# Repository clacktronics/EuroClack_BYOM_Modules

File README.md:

# BYOM Modules

In this repository is all the modules in the book for **Build Your Own Modular** the Clacktronics ring binder product to build your own modular synthesizer from scratch. [clacktronics.co.uk/byom/](http://clacktronics.co.uk/byom/). These are the original project files PCB and panel With branding removed, they are not the pages which are panels I make up from these files. It does not include the text of the book either. I have provided these as a starting point for your own projects and ideas, I do not mind if they are used commercially, all I ask for is attribution to my original physical design and for them not to be sold under my brand name **Clacktronics**.

## PSU

A simple PSU that uses the 12V direct and creates a -12V using a cheap through hole MC34063

[PSU Schematic](pdf_schematics/BYOM_PSU_main.pdf)

## VCO

A paired down sawtooth VCO that can do a couple of octaves, uses only TL074

[VCO Schematic](pdf_schematics/BYOM_VCO_main.pdf)

## VCA

Simple dual VCA using the LM13700

[VCA Schematic](pdf_schematics/BYOM_VCA_main.pdf)

## VCF

A gritty sounding VCF using the LM13700

[VCF Schematic](pdf_schematics/BYOM_VCF_main.pdf)

## ATTENUVERTER

Performs basic attunuation and inversion of CV signals

[Attenuverter Schematic](pdf_schematics/BYOM_Attenuverter_main.pdf)

## MIXER

Mixes CV and Audio signals

[Mixer Schematic](pdf_schematics/BYOM_Mixer_main.pdf)

## LFO

Simple LFO that has shape and frequency controls

[LFO Schematic](pdf_schematics/BYOM_LFO_main.pdf)

## ENVELOPE

Simple AR generator

[Envelope Schematic](pdf_schematics/BYOM_Envelope_main.pdf)

## MICROCONTROLLER

Raspberry Pi Pico based experimental board

[Micro Schematic](pdf_schematics/BYOM_Micro_main.pdf)

## PASSIVE MULT

Helps connect CV outputs together

## POWER BUS

Simple passive power bus

## BLANK

Pretty blank plate

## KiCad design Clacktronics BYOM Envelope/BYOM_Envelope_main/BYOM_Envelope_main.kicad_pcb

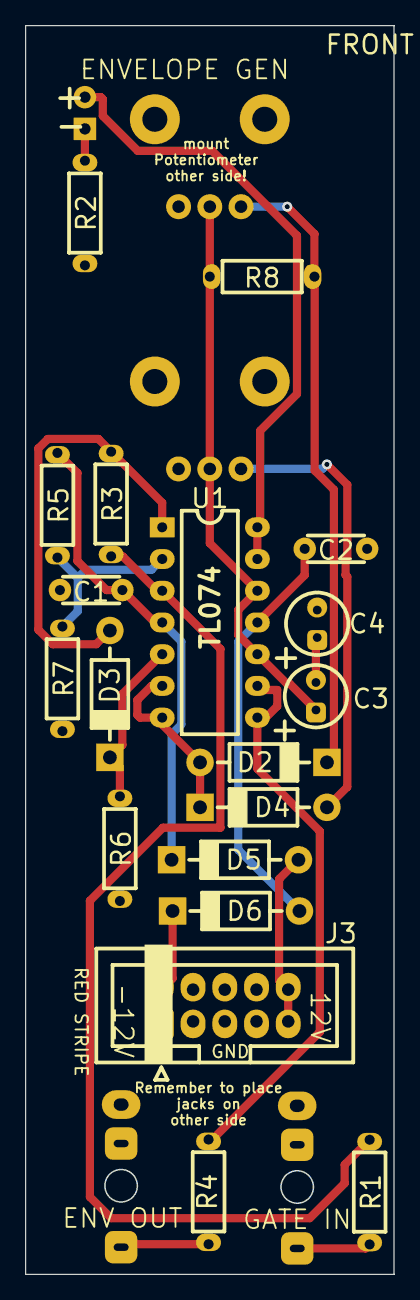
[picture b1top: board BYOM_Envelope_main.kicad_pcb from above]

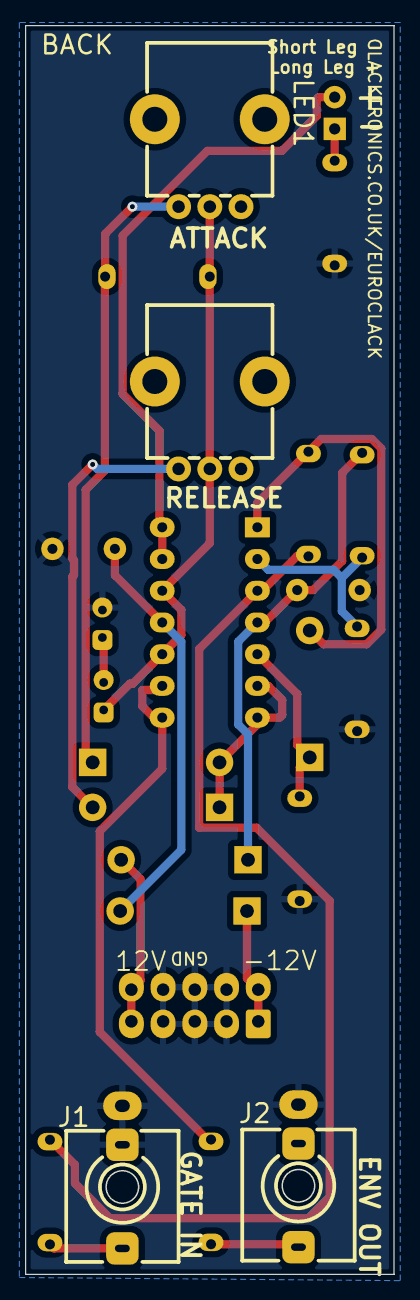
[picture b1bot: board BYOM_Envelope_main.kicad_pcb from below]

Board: 2 copper layers, 29.5 x 100.0 mm, 24 parts (5 on the bottom side), 19 nets.

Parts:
C1, C2: 100n; C_TH_Disc_P5.00mm
C3, C4: 100uF; C_TH_Elec_5mm_P2mm
D2, D3, D4, D5, D6: 1N5817; D_TH_DO-41_P10.16mm
J1: GATE_IN; Jack_3.5mm_QingPu_WQP-PJ398SM_Vertical
J2: AR_ENVELOPE_OUT; Jack_3.5mm_QingPu_WQP-PJ398SM_Vertical
J3: IDC 02x05 Header; IDC-Header_2x05_P2.54mm_Vertical
LED1: LED; LED_D3.0mm
R1, R5, R6: 100k; R_Axial_DIN0204_L3.6mm_D1.6mm_P7.62mm_Horizontal
R2, R4: 1k; R_Axial_DIN0204_L3.6mm_D1.6mm_P7.62mm_Horizontal
R3: 1M; R_Axial_DIN0204_L3.6mm_D1.6mm_P7.62mm_Horizontal
R7, R8: 10k; R_Axial_DIN0204_L3.6mm_D1.6mm_P7.62mm_Horizontal
RV1: Attack; POT_TH_Alps_RK09K_Single_Vertical
RV2: Release; POT_TH_Alps_RK09K_Single_Vertical
U1: TL074; DIP-14_W7.62mm_LongPads_copy

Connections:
+12V: C1.2, D5.1 (K), R5.2, U1.4 (V+)
-12V: C2.2, D6.2 (A), U1.11 (V-)
GND: C1.1, C2.1, C4.2, J1.S, J1.TN, J2.S, J3.3, J3.4, J3.5, J3.6, J3.7, J3.8, R2.1, R6.1, R7.1
unnamed: C3.2, C4.1
unnamed: D2.2 (A), D4.1 (K), U1.6 (-), U1.7
unnamed: D2.1 (K), R8.2, RV1.3
unnamed: D3.2 (A), R3.2, U1.1
unnamed: D3.1 (K), R6.2, U1.5 (+)
unnamed: D4.2 (A), RV2.3
unnamed: D5.2 (A), J3.9, J3.10
unnamed: D6.1 (K), J3.1, J3.2
unnamed: J1.T, R1.1
unnamed: J2.T, R4.2
unnamed: LED1.2 (A), U1.13 (-), U1.14
unnamed: LED1.1 (K), R2.2
unnamed: R1.2, R3.1, U1.3 (+)
unnamed: R5.1, R7.2, U1.2 (-)
unnamed: C3.1, R8.1, RV1.2, RV2.2, U1.10 (+), U1.12 (+)
unnamed: R4.1, U1.8, U1.9 (-)

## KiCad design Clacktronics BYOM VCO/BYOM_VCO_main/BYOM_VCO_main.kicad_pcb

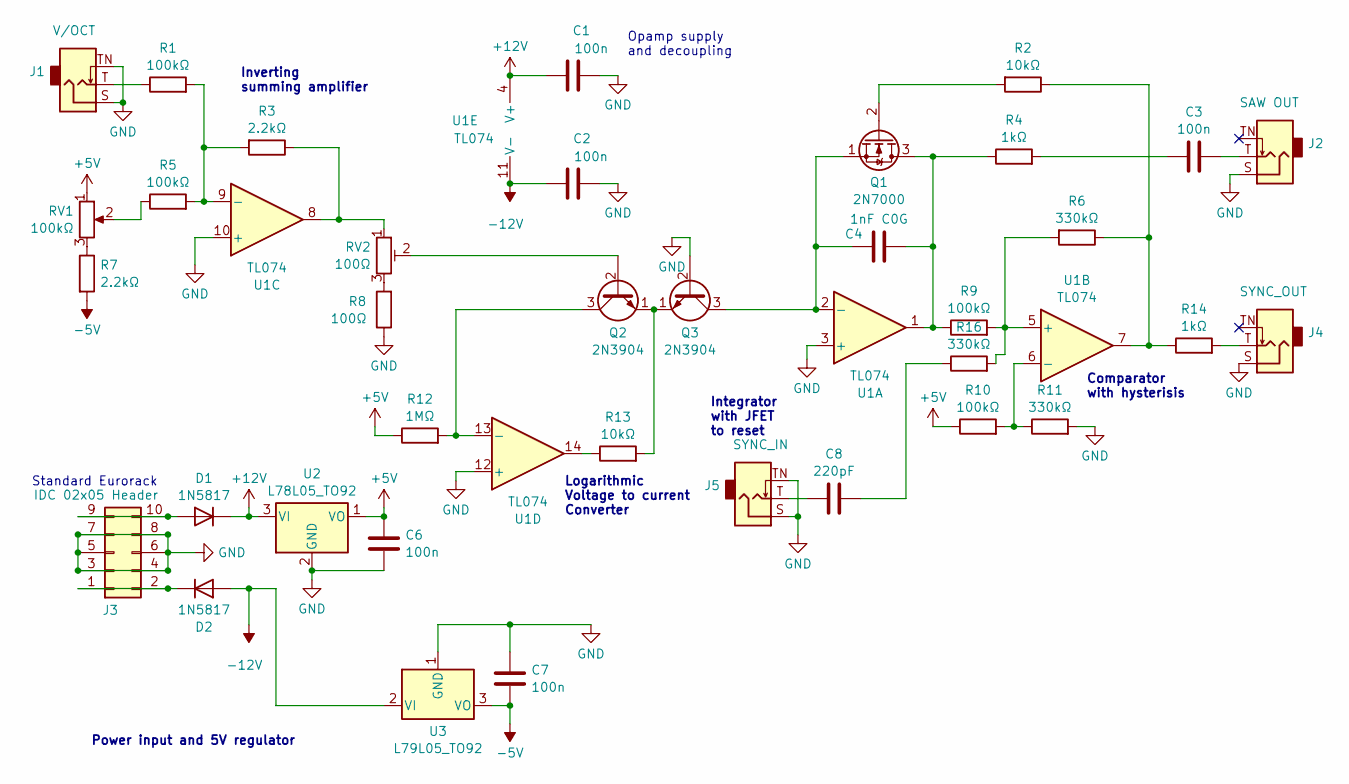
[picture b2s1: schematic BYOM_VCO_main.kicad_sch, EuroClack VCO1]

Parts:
C1, C2, C3, C6, C7: 100n; C_TH_Disc_P5.00mm
C4: 1nF C0G; C_TH_Disc_P5.00mm
C8: 220pF; C_TH_Disc_P5.00mm
D1, D2: 1N5817; D_TH_DO-41_P10.16mm
J1: V/OCT; Jack_3.5mm_QingPu_WQP-PJ398SM_Vertical
J2: SAW OUT; Jack_3.5mm_QingPu_WQP-PJ398SM_Vertical
J3: IDC 02x05 Header; IDC-Header_2x05_P2.54mm_Vertical
J4: SYNC_OUT; Jack_3.5mm_QingPu_WQP-PJ398SM_Vertical
J5: SYNC_IN; Jack_3.5mm_QingPu_WQP-PJ398SM_Vertical
Q1: 2N7000; TO-92_Inline_Wide
Q2, Q3: 2N3904; TO-92_Inline_Wide
R1, R5, R9, R10: 100kΩ; R_Axial_DIN0204_L3.6mm_D1.6mm_P7.62mm_Horizontal
R2, R13: 10kΩ; R_Axial_DIN0204_L3.6mm_D1.6mm_P7.62mm_Horizontal
R3, R7: 2.2kΩ; R_Axial_DIN0204_L3.6mm_D1.6mm_P7.62mm_Horizontal
R4, R14: 1kΩ; R_Axial_DIN0204_L3.6mm_D1.6mm_P7.62mm_Horizontal
R6, R11, R16: 330kΩ; R_Axial_DIN0204_L3.6mm_D1.6mm_P7.62mm_Horizontal
R8: 100Ω; R_Axial_DIN0204_L3.6mm_D1.6mm_P7.62mm_Horizontal
R12: 1MΩ; R_Axial_DIN0204_L3.6mm_D1.6mm_P7.62mm_Horizontal
RV1: 100kΩ; POT_TH_Alps_RK09K_Single_Vertical
RV2: 100Ω; Potentiometer_Bourns_3296W_Vertical
U1: TL074; DIP-14_W7.62mm_LongPads_copy
U2: L78L05_TO92; TO-92_Inline_Wide
U3: L79L05_TO92; TO-92_Inline_Wide

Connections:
+5V: C6.2, R10.1, R12.1, RV1.1, U2.1 (VO)
+12V: C1.2, D1.1 (K), U1.4 (V+), U2.3 (VI)
-5V: C7.1, R7.2, U3.3 (VO)
-12V: C2.2, D2.2 (A), U1.11 (V-), U3.2 (VI)
GND: C1.1, C2.1, C6.1, C7.2, J1.S, J1.TN, J2.S, J3.3, J3.4, J3.5, J3.6, J3.7, J3.8, J4.S, J5.S, J5.TN, Q3.2 (B), R8.1, R11.2, U1.3 (+), U1.10 (+), U1.12 (+), U2.2 (GND), U3.1 (GND)
unnamed: C3.1, R4.2
unnamed: C3.2, J2.T
unnamed: C8.1, J5.T
unnamed: C8.2, R16.1
unnamed: D1.2 (A), J3.9, J3.10
unnamed: D2.1 (K), J3.1, J3.2
unnamed: J1.T, R1.1
unnamed: J4.T, R14.2
unnamed: C4.2, Q1.3 (D), R4.1, R9.1, U1.1
unnamed: Q1.2 (G), R2.2
unnamed: C4.1, Q1.1 (S), Q3.3 (C), U1.2 (-)
unnamed: Q2.2 (B), RV2.2
unnamed: Q2.3 (C), R12.2, U1.13 (-)
unnamed: Q2.1 (E), Q3.1 (E), R13.2
unnamed: R3.1, RV2.1, U1.8
unnamed: R5.1, RV1.2
unnamed: R7.1, RV1.3
unnamed: R8.2, RV2.3
unnamed: R13.1, U1.14
unnamed: R2.1, R6.1, R14.1, U1.7
unnamed: R6.2, R9.2, R16.2, U1.5 (+)
unnamed: R10.2, R11.1, U1.6 (-)
unnamed: R1.2, R3.2, R5.2, U1.9 (-)

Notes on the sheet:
Standard Eurorack
Logarithmic Voltage to current Converter
Opamp supply and decoupling
Comparator with hysterisis
Power input and 5V regulator
Integrator with JFET to reset
Inverting summing amplifier

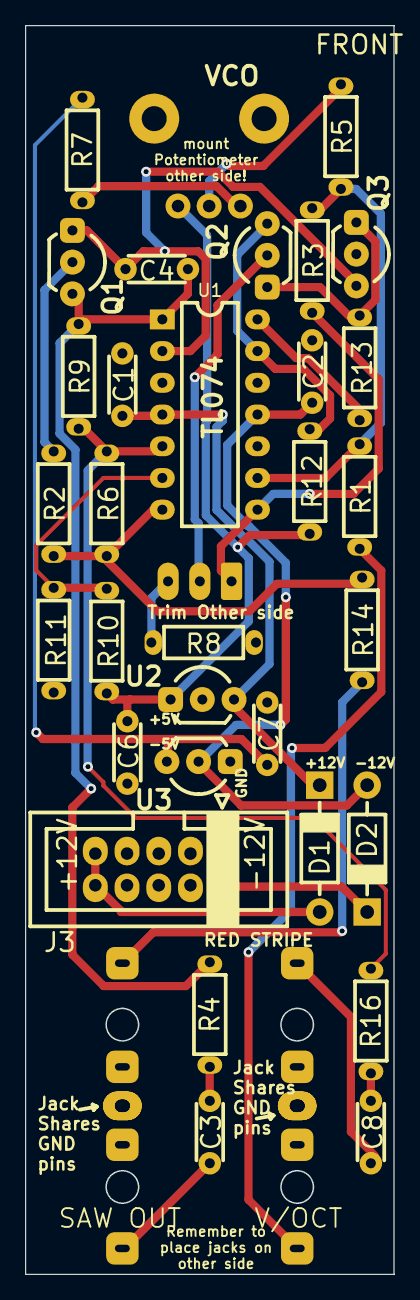
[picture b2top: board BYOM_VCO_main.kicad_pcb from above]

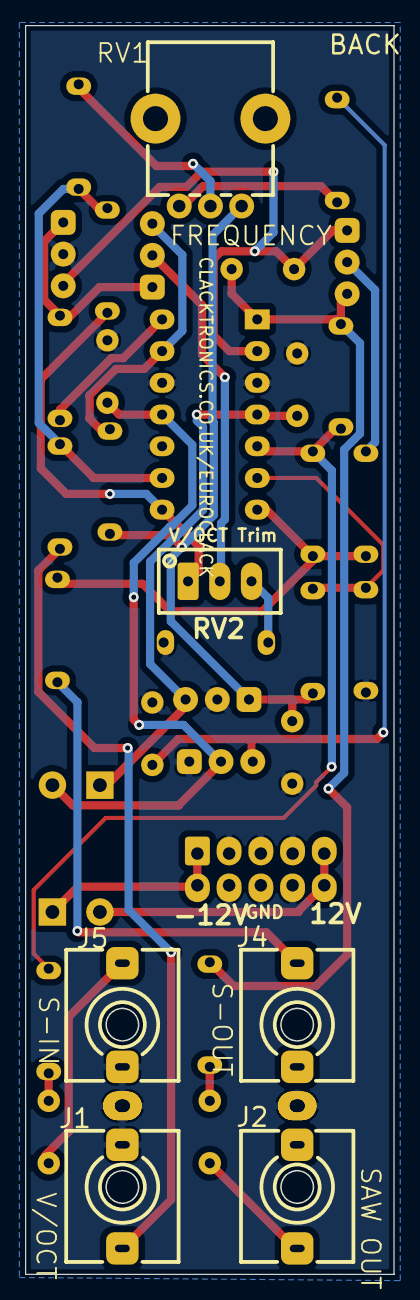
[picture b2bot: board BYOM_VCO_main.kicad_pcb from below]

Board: 2 copper layers, 29.5 x 100.0 mm, 37 parts (6 on the bottom side), 28 nets.

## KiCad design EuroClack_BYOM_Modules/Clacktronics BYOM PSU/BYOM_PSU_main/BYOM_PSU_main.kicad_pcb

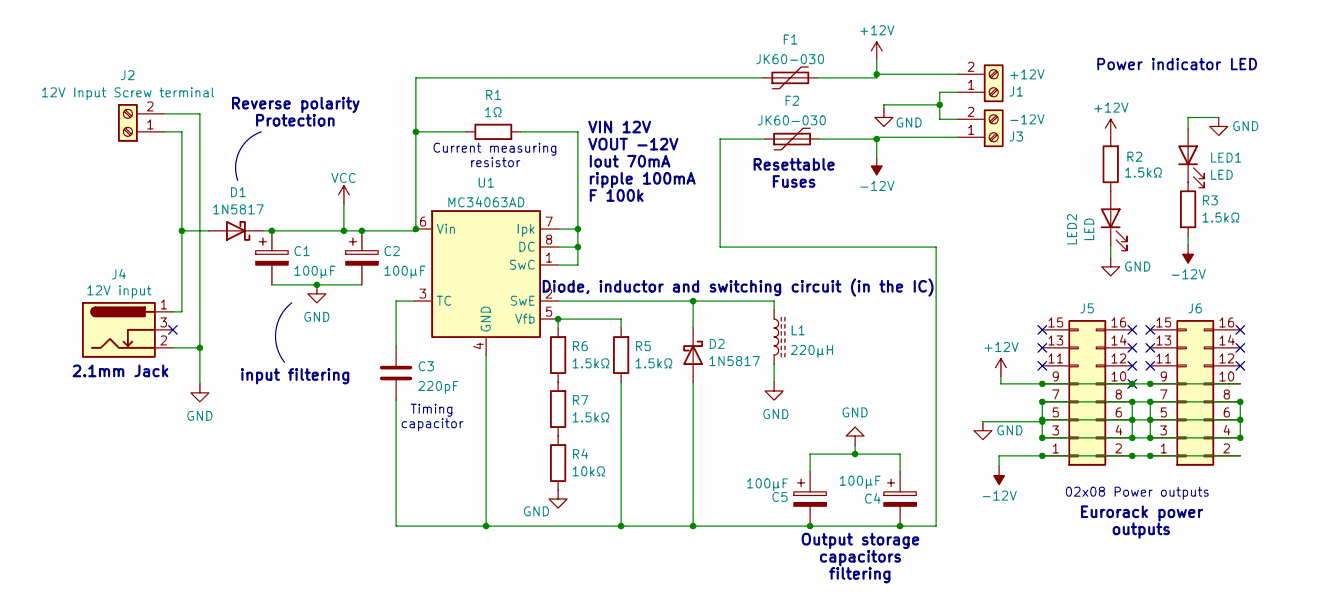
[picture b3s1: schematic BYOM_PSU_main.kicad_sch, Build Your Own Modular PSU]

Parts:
C1, C2, C4, C5: 100μF; C_TH_Elec_5mm_P2mm
C3: 220pF; C_TH_Disc_P5.00mm
D1, D2: 1N5817; D_TH_DO-41_P10.16mm
F1, F2: JK60-030; C_TH_Disc_P5.00mm
J1: +12V; 5.08 01X02
J2: 12V Input Screw terminal; 5.08 01X02
J3: -12V; 5.08 01X02
J4: 12V input; DC-IN-TH_DC-012A-20A
J5, J6: EURORACK_16_PIN; IDC-Header_2x08_P2.54mm_Vertical
L1: 220μH; L_Radial_D10.0mm_P5.00mm_Neosid_SD12_style3
LED1, LED2: LED; LED_D3.0mm
R1: 1Ω; R_TH_Axial_250mw_P10.16mm_Horizontal
R2, R3, R5, R6, R7: 1.5kΩ; R_TH_Axial_250mw_P10.16mm_Horizontal
R4: 10kΩ; R_TH_Axial_250mw_P10.16mm_Horizontal
U1: MC34063AD; DIP-8_W7.62mm_LongPads

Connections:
+12V: F1.2, J1.2, J5.9, J5.10, J6.9, J6.10, R2.2
-12V: F2.2, J3.1, J5.1, J5.2, J6.1, J6.2, R3.2
GND: C1.2, C2.2, C4.1, C5.1, J1.1, J2.2, J3.2, J4.2, J5.3, J5.4, J5.5, J5.6, J5.7, J5.8, J6.3, J6.4, J6.5, J6.6, J6.7, J6.8, L1.2, LED1.2 (A), LED2.1 (K), R4.1
unnamed: D1.2 (A), J2.1, J4.1
unnamed: C3.2, C4.2, C5.2, D2.2 (A), F2.1, R5.1, U1.4 (GND)
unnamed: D2.1 (K), L1.1, U1.2 (SwE)
unnamed: LED1.1 (K), R3.1
unnamed: LED2.2 (A), R2.1
unnamed: R4.2, R7.1
unnamed: R6.1, R7.2
unnamed: R1.2, U1.1 (SwC), U1.7 (Ipk), U1.8 (DC)
unnamed: C3.1, U1.3 (TC)
unnamed: R5.2, R6.2, U1.5 (Vfb)
VCC: C1.1, C2.1, D1.1 (K), F1.1, R1.1, U1.6 (Vin)

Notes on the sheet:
2.1mm Jack
02x08 Power outputs
input filtering
Timing capacitor
Current measuring resistor
Eurorack power outputs
VIN 12V VOUT -12V Iout 70mA ripple 100mA F 100k
Diode, inductor and switching circuit (in the IC)
Reverse polarity Protection
Resettable Fuses
Output storage capacitors filtering
Power indicator LED

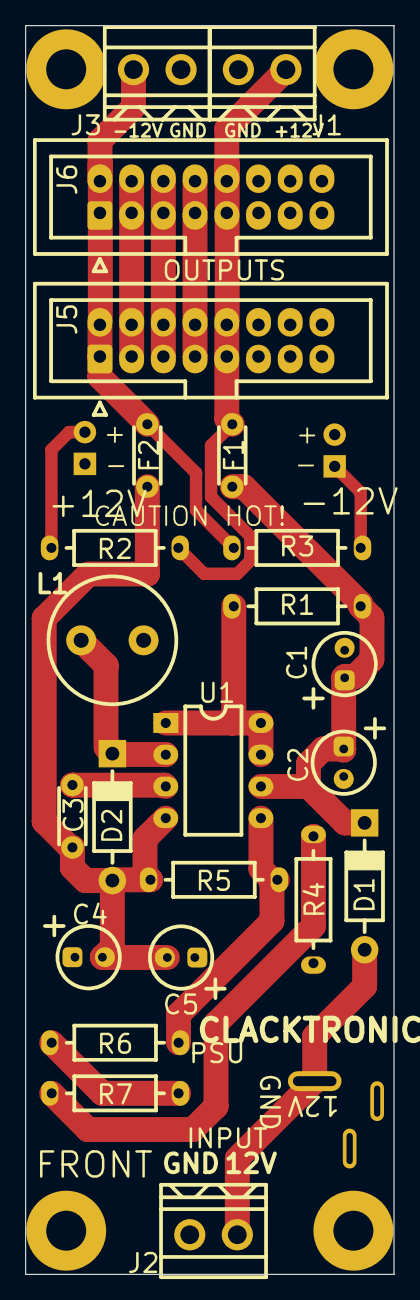
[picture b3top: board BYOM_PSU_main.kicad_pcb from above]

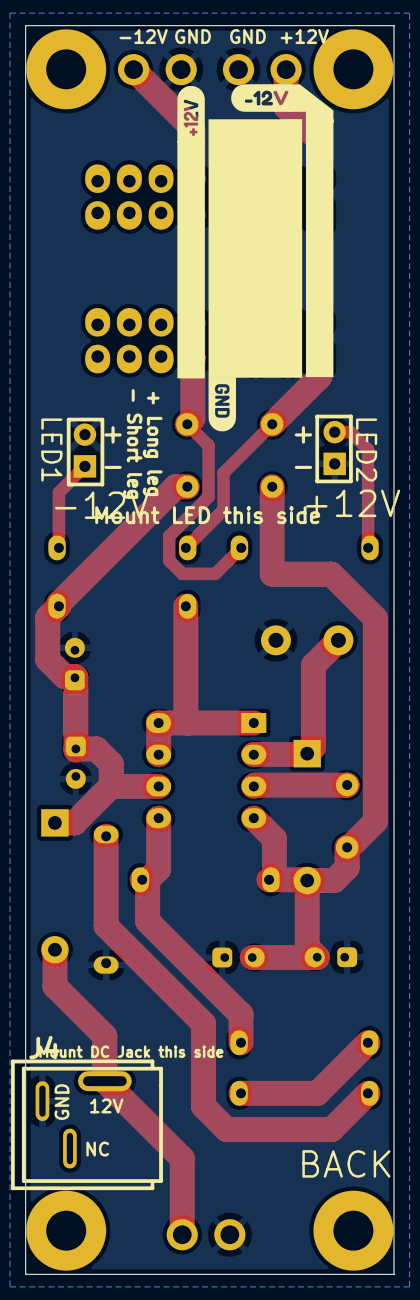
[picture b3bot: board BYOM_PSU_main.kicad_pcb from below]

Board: 2 copper layers, 29.5 x 100.0 mm, 29 parts (6 on the bottom side), 14 nets.

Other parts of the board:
kibuzzard-63C1369E: G***; kibuzzard-63C1369E
kibuzzard-63C13629: G***; kibuzzard-63C13629
kibuzzard-6399AAFB: G***; kibuzzard-6399AAFB

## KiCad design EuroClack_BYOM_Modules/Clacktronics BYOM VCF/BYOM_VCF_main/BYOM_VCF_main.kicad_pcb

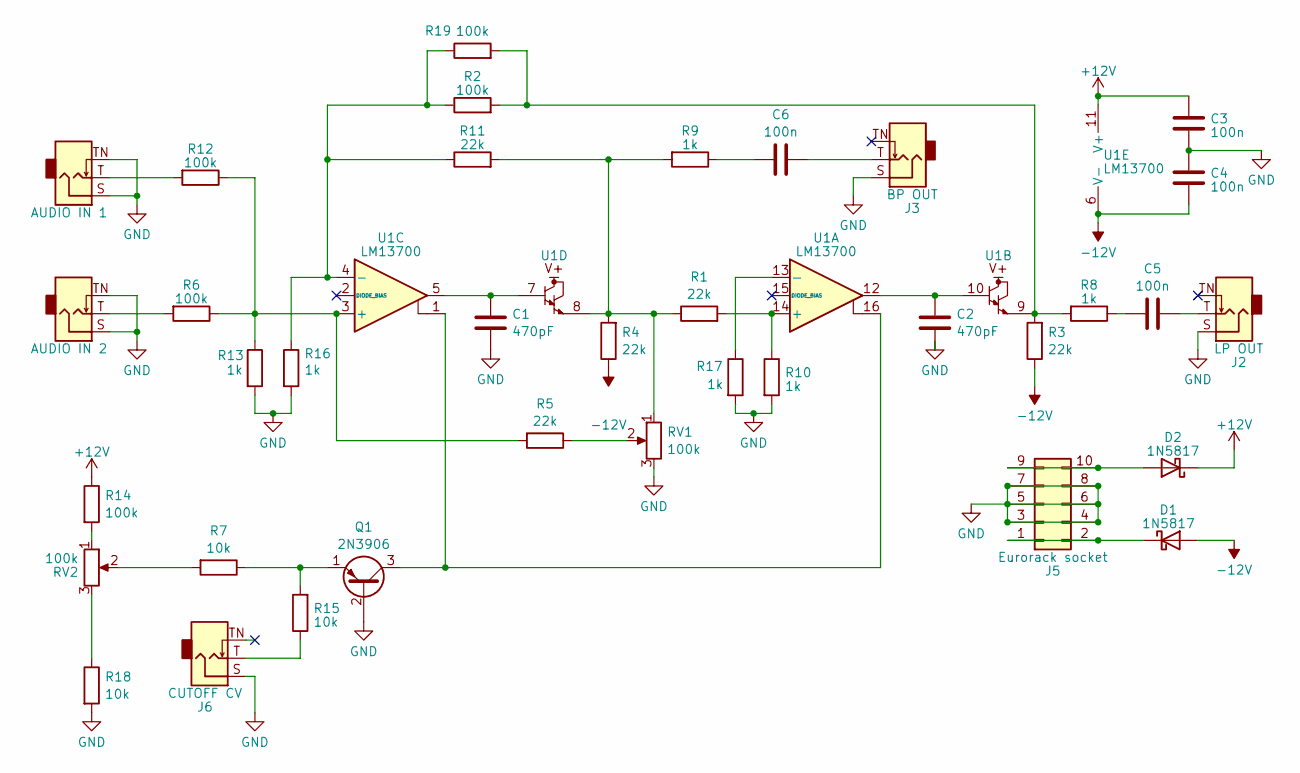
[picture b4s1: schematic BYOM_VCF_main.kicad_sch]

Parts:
C1, C2: 470pF; C_TH_Disc_P5.00mm
C3, C4, C5, C6: 100n; C_TH_Disc_P5.00mm
D1, D2: 1N5817; D_TH_DO-41_P10.16mm
J1: AUDIO IN 2; Jack_3.5mm_QingPu_WQP-PJ398SM_Vertical
J2: LP OUT; Jack_3.5mm_QingPu_WQP-PJ398SM_Vertical
J3: BP OUT; Jack_3.5mm_QingPu_WQP-PJ398SM_Vertical
J4: AUDIO IN 1; Jack_3.5mm_QingPu_WQP-PJ398SM_Vertical
J5: Eurorack socket; IDC-Header_2x05_P2.54mm_Vertical
J6: CUTOFF CV; Jack_3.5mm_QingPu_WQP-PJ398SM_Vertical
Q1: 2N3906; TO-92_Inline_Wide
R1, R3, R4, R5, R11: 22k; R_Axial_DIN0204_L3.6mm_D1.6mm_P7.62mm_Horizontal
R2, R6, R12, R14, R19: 100k; R_Axial_DIN0204_L3.6mm_D1.6mm_P7.62mm_Horizontal
R7, R15, R18: 10k; R_Axial_DIN0204_L3.6mm_D1.6mm_P7.62mm_Horizontal
R8, R9, R10, R13, R16, R17: 1k; R_Axial_DIN0204_L3.6mm_D1.6mm_P7.62mm_Horizontal
RV1, RV2: 100k; POT_TH_Alps_RK09K_Single_Vertical
U1: LM13700; DIP-16_W7.62mm_LongPads

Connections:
+12V: C3.1, D2.1 (K), R14.1, U1.11 (V+)
-12V: C4.2, D1.2 (A), R3.1, R4.1, U1.6 (V-)
GND: C1.2, C2.2, C3.2, C4.1, J1.S, J1.TN, J2.S, J3.S, J4.S, J4.TN, J5.3, J5.4, J5.5, J5.6, J5.7, J5.8, J6.S, Q1.2 (B), R10.2, R13.2, R16.2, R17.2, R18.2, RV1.3
unnamed: C1.1, U1.5, U1.7
unnamed: C2.1, U1.10, U1.12
unnamed: C5.1, R8.1
unnamed: C5.2, J2.T
unnamed: C6.1, R9.1
unnamed: C6.2, J3.T
unnamed: D1.1 (K), J5.1, J5.2
unnamed: D2.2 (A), J5.9, J5.10
unnamed: J1.T, R6.2
unnamed: J4.T, R12.2
unnamed: J6.T, R15.1
unnamed: Q1.3 (C), U1.1, U1.16
unnamed: Q1.1 (E), R7.1, R15.2
unnamed: R1.1, R4.2, R9.2, R11.2, RV1.1, U1.8
unnamed: R5.1, RV1.2
unnamed: R7.2, RV2.2
unnamed: R14.2, RV2.1
unnamed: R18.1, RV2.3
unnamed: R2.2, R3.2, R8.2, R19.2, U1.9
unnamed: R1.2, R10.1, U1.14 (+)
unnamed: R17.1, U1.13 (-)
unnamed: R5.2, R6.1, R12.1, R13.1, U1.3 (+)
unnamed: R2.1, R11.1, R16.1, R19.1, U1.4 (-)

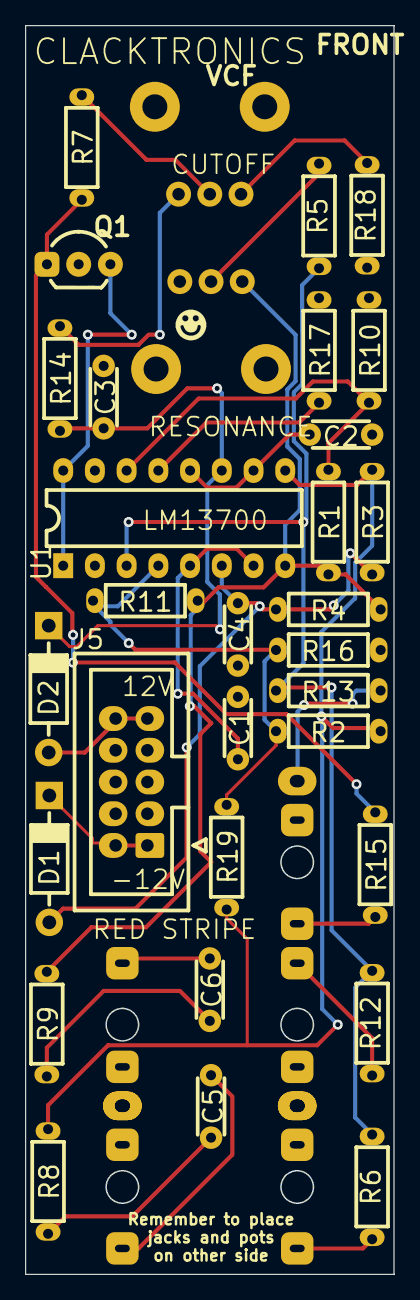
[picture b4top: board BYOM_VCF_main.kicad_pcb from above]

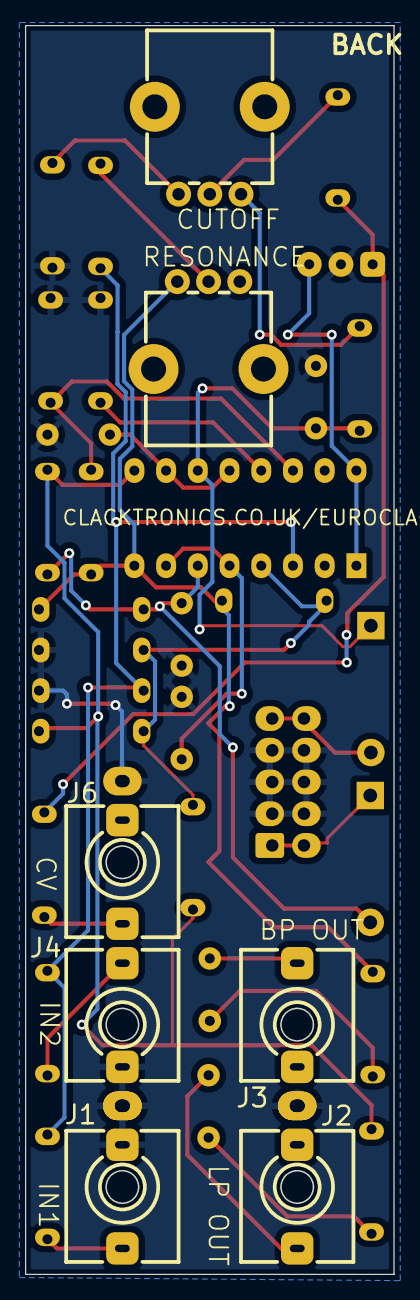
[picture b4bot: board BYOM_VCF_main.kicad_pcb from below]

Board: 2 copper layers, 29.5 x 100.0 mm, 37 parts (7 on the bottom side), 26 nets.

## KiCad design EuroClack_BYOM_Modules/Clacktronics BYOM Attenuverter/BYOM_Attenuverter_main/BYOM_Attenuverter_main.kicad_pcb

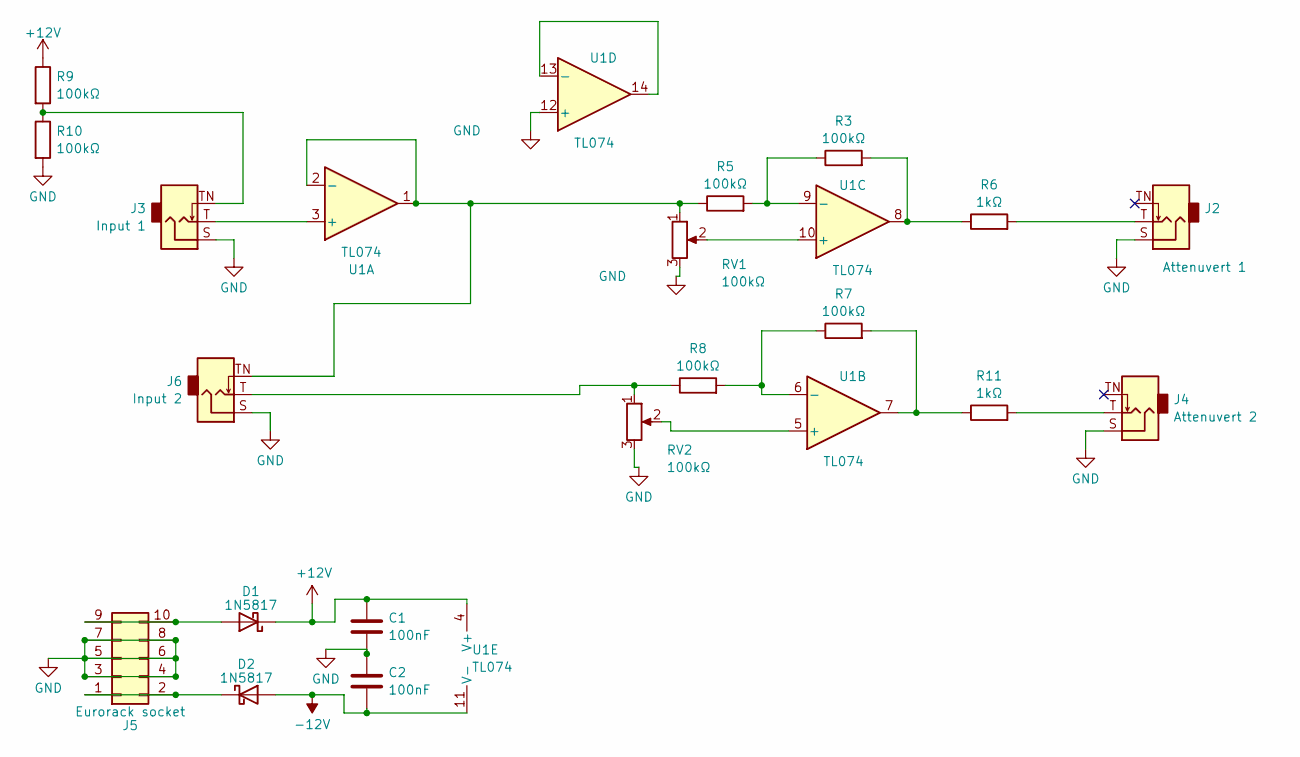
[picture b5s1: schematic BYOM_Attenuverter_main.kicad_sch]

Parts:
C1, C2: 100nF; C_TH_Disc_P5.00mm
D1, D2: 1N5817; D_TH_DO-41_P10.16mm
J2: Attenuvert 1; Jack_3.5mm_QingPu_WQP-PJ398SM_Vertical
J3: Input 1; Jack_3.5mm_QingPu_WQP-PJ398SM_Vertical
J4: Attenuvert 2; Jack_3.5mm_QingPu_WQP-PJ398SM_Vertical
J5: Eurorack socket; IDC-Header_2x05_P2.54mm_Vertical
J6: Input 2; Jack_3.5mm_QingPu_WQP-PJ398SM_Vertical
R3, R5, R7, R8, R9, R10: 100kΩ; R_Axial_DIN0204_L3.6mm_D1.6mm_P7.62mm_Horizontal
R6, R11: 1kΩ; R_Axial_DIN0204_L3.6mm_D1.6mm_P7.62mm_Horizontal
RV1, RV2: 100kΩ; POT_TH_Alps_RK09K_Single_Vertical
U1: TL074; DIP-14_W7.62mm_LongPads_copy

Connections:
+12V: C1.1, D1.1 (K), R9.1, U1.4 (V+)
-12V: C2.2, D2.2 (A), U1.11 (V-)
GND: C1.2, C2.1, J2.S, J3.S, J4.S, J5.3, J5.4, J5.5, J5.6, J5.7, J5.8, J6.S, R10.2, RV1.3, RV2.3, U1.12 (+)
unnamed: D1.2 (A), J5.9, J5.10
unnamed: D2.1 (K), J5.1, J5.2
unnamed: J2.T, R6.2
unnamed: J3.TN, R9.2, R10.1
unnamed: J4.T, R11.2
unnamed: J6.T, R8.1, RV2.1
unnamed: R3.2, R6.1, U1.8
unnamed: R7.2, R11.1, U1.7
unnamed: J3.T, U1.3 (+)
unnamed: J6.TN, R5.1, RV1.1, U1.1, U1.2 (-)
unnamed: RV2.2, U1.5 (+)
unnamed: R7.1, R8.2, U1.6 (-)
unnamed: RV1.2, U1.10 (+)
unnamed: R3.1, R5.2, U1.9 (-)
unnamed: U1.13 (-), U1.14

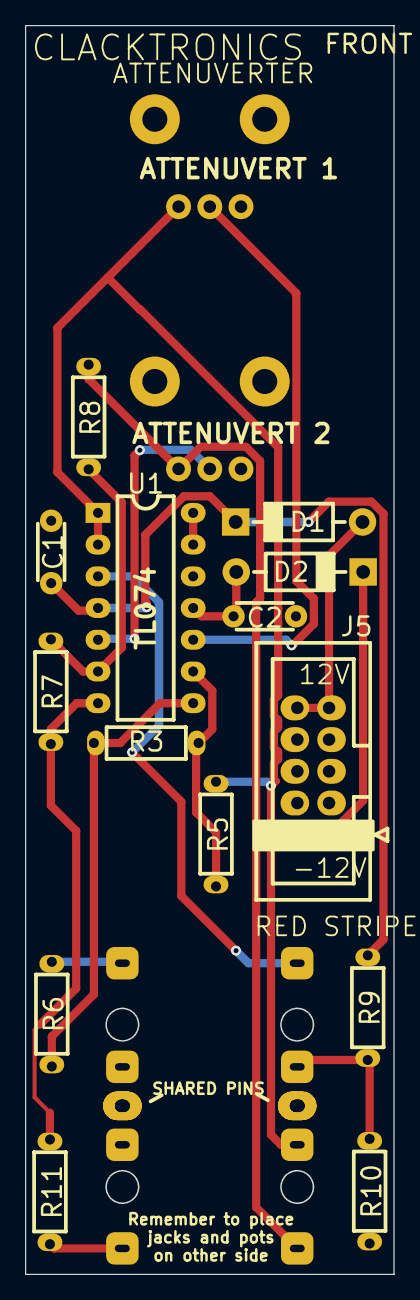
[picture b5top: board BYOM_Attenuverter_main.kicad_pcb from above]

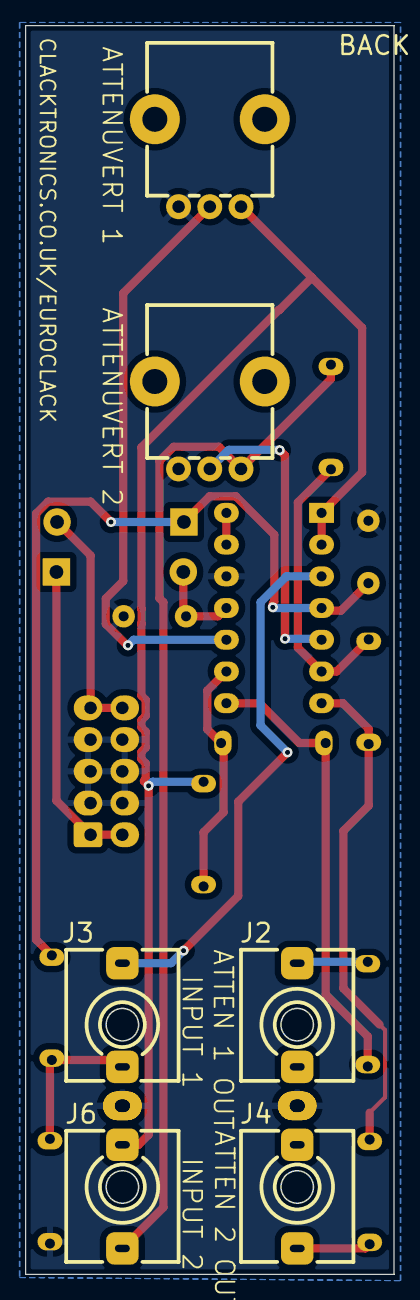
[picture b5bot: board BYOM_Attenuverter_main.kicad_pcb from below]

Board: 2 copper layers, 29.5 x 100.0 mm, 20 parts (6 on the bottom side), 18 nets.

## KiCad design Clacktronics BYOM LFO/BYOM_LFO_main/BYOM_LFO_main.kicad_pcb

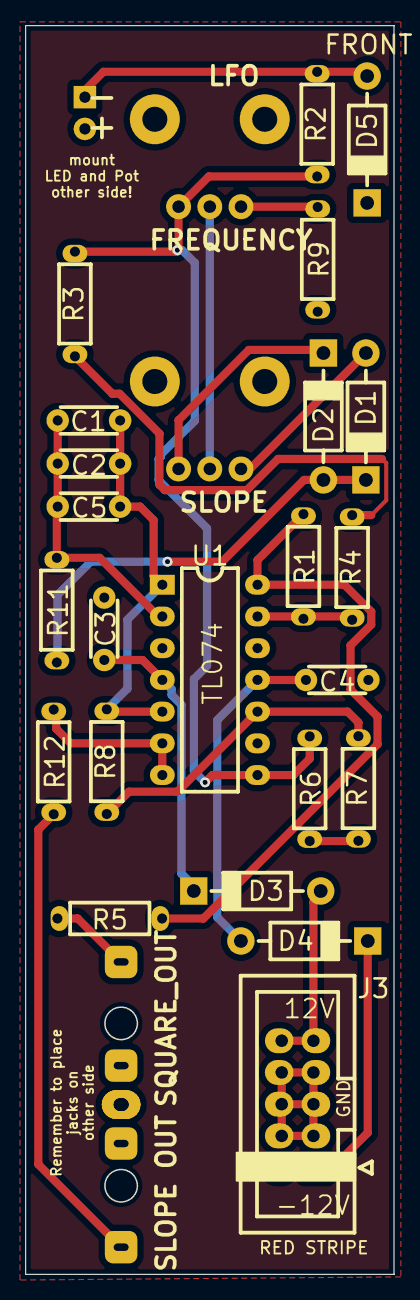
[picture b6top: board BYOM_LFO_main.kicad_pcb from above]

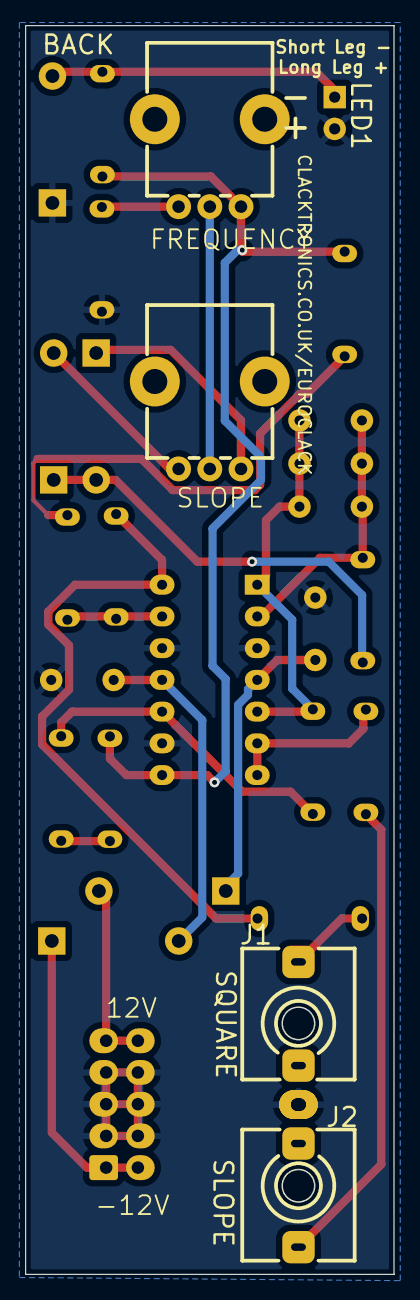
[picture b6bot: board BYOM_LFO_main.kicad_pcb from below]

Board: 2 copper layers, 29.5 x 100.0 mm, 28 parts (5 on the bottom side), 22 nets.

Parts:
C1, C2, C3, C4, C5: 100nF; C_TH_Disc_P5.00mm
D1, D2, D3, D4, D5: 1N5817; D_TH_DO-41_P10.16mm
J1: SQUARE OUT; Jack_3.5mm_QingPu_WQP-PJ398SM_Vertical
J2: SLOPE OUT; Jack_3.5mm_QingPu_WQP-PJ398SM_Vertical
J3: Conn_02x05_Odd_Even; IDC-Header_2x05_P2.54mm_Vertical
LED1: LED; LED_D3.0mm
R1, R3, R4, R6, R7, R8: 100kΩ; R_Axial_DIN0204_L3.6mm_D1.6mm_P7.62mm_Horizontal
R2: 2.2KΩ; R_Axial_DIN0204_L3.6mm_D1.6mm_P7.62mm_Horizontal
R5, R12: 1kΩ; R_Axial_DIN0204_L3.6mm_D1.6mm_P7.62mm_Horizontal
R9, R11: 100Ω; R_Axial_DIN0204_L3.6mm_D1.6mm_P7.62mm_Horizontal
RV1, RV2: 100kΩ; POT_TH_Alps_RK09K_Single_Vertical
U1: TL074; DIP-14_W7.62mm_LongPads_copy

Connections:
+12V: C3.2, D3.1 (K), U1.4 (V+)
-12V: C4.1, D4.2 (A), U1.11 (V-)
GND: C3.1, C4.2, D5.1 (K), J1.S, J2.S, J3.3, J3.4, J3.5, J3.6, J3.7, J3.8, LED1.2 (A), R9.1, U1.3 (+), U1.9 (-), U1.12 (+)
unnamed: D1.2 (A), RV1.3
unnamed: D1.1 (K), D2.2 (A), R11.1
unnamed: D2.1 (K), RV1.1
unnamed: D3.2 (A), J3.9, J3.10
unnamed: D4.1 (K), J3.1, J3.2
unnamed: D5.2 (A), LED1.1 (K), R2.1
unnamed: J1.T, R5.1
unnamed: J2.T, R12.1
unnamed: R1.2, R5.2, U1.14
unnamed: R2.2, R3.1, R6.2, RV2.1, U1.8
unnamed: R3.2, R4.1
unnamed: R6.1, R7.2
unnamed: R9.2, RV2.3
unnamed: RV1.2, RV2.2
unnamed: C1.2, C2.2, C5.2, R11.2, U1.2 (-)
unnamed: C1.1, C2.1, C5.1, R8.1, U1.1, U1.5 (+)
unnamed: R12.2, U1.6 (-), U1.7
unnamed: R7.1, R8.2, U1.10 (+)
unnamed: R1.1, R4.2, U1.13 (-)

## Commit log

2024-11-14 initial
2024-11-15 Modifications, added readme
2024-11-15 edit readme
2024-11-15 Added spacing
2024-11-15 fixed readme error
2024-11-15 fixed error in LFO schematic
2025-01-29 Error in envelope schamtic, shows TL072 instead of TL074
2025-01-29 file cleanup
